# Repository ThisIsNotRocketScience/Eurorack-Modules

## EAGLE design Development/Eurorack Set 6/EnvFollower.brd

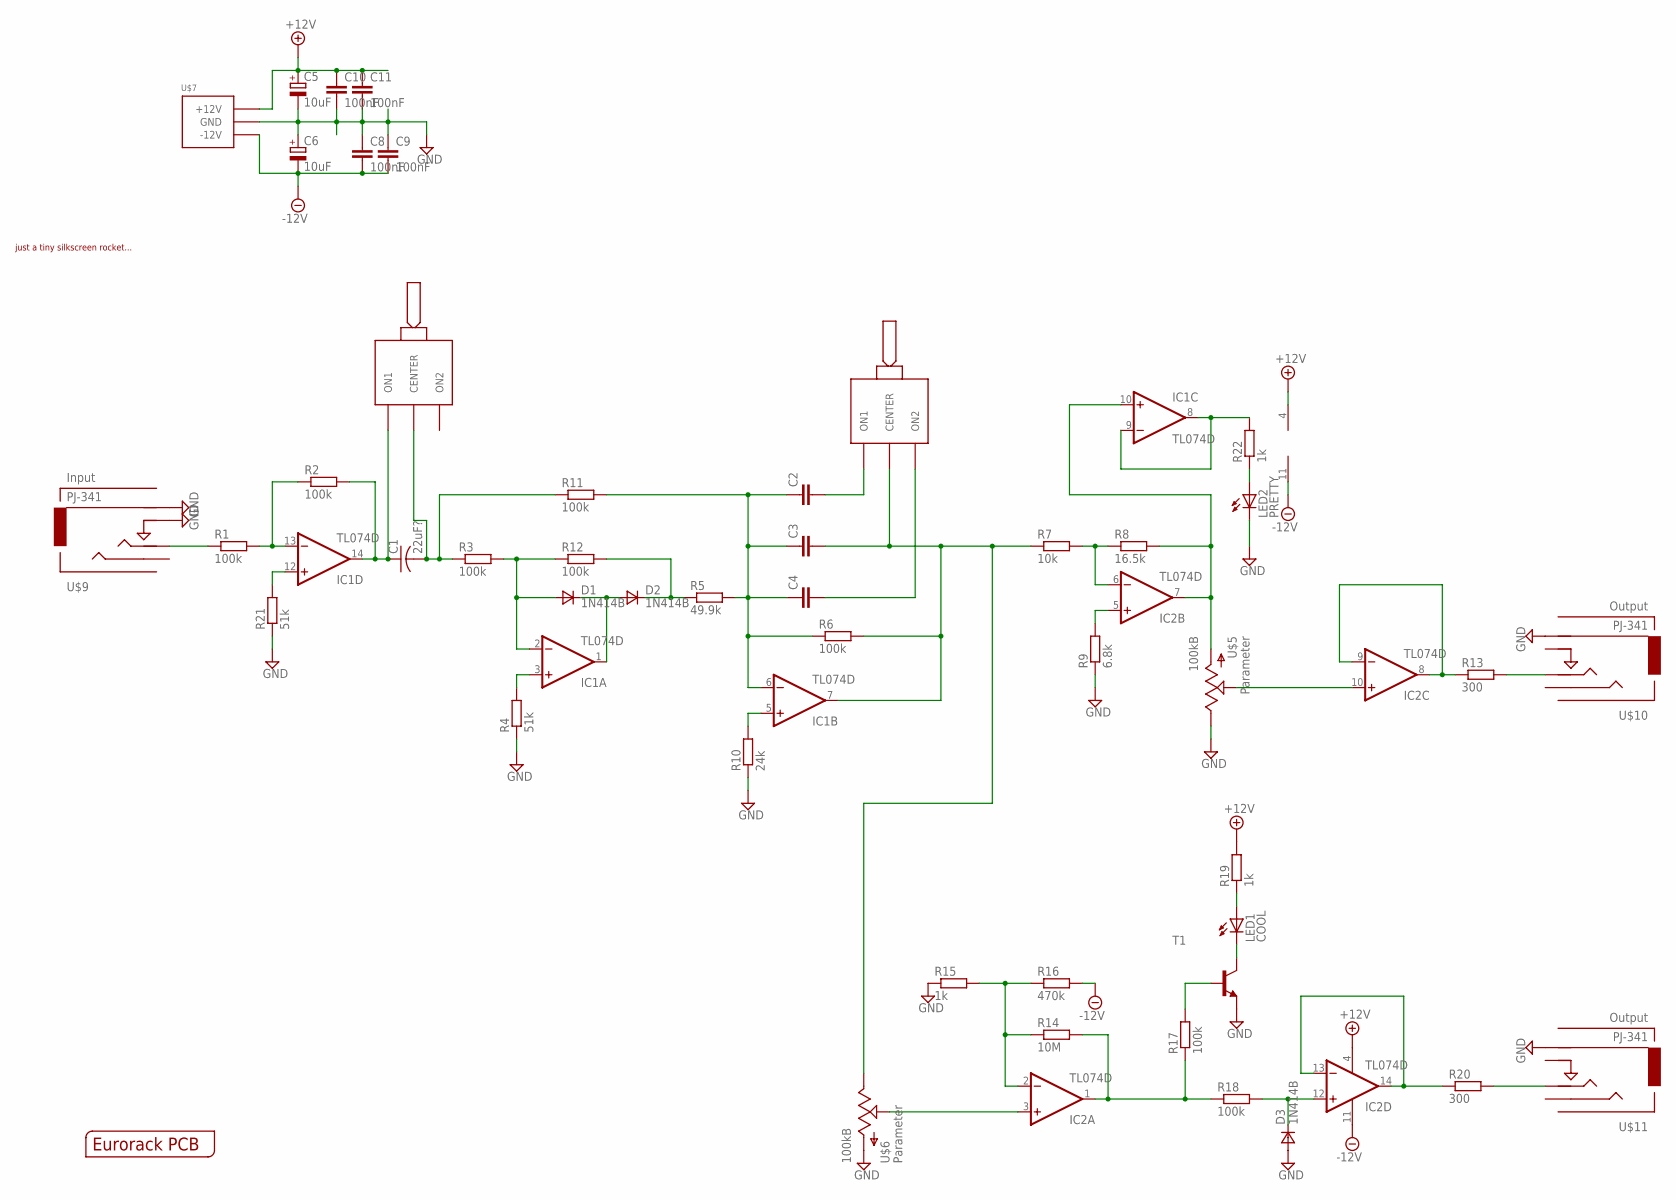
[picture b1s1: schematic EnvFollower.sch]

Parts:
C1: 22uF?; C1210K
C2, C3, C4: C-EUC0603K; C0603K
C5, C6: 10uF; 153CLV-0505
C8, C9, C10, C11: 100nF; C0603K
D1, D2, D3: 1N414B; SOT-23
IC1, IC2: TL074D; SO14
LED1: COOL; LED3MM
LED2: PRETTY; LED3MM
R1, R2, R3, R6, R11, R12, R17, R18: 100k; R0603
R4, R21: 51k; R0603
R5: 49.9k; R0603
R7: 10k; R0603
R8: 16.5k; R0603
R9: 6.8k; R0603
R10: 24k; R0603
R13, R20: 300; R0603
R14: 10M; R0603
R15, R19, R22: 1k; R0603
R16: 470k; R0603
T1: BCX70-NPN-SOT23-BEC; SOT23-BEC
U$1: EURORACK_PCB4HP; EURORACK4HPPCB
U$2: JUSTATINYROCKET
U$4, U$8: ONOFFON; MULTICOMP1MS-ONOFFON
U$5, U$6: 100kB; OG-POTS_ALPS_POT_VERTICAL
U$7: POWER_SIMPLE10-OTHERSIDE; POWER_10_LABELSOTHERSIDE
U$9: PJ-341; 3.5MM-JACK-SWITCH-13MM-INPUT
U$10, U$11: PJ-341; 3.5MM-JACK-SWITCH-13MM-OUTPUT

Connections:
+12V: C5.+, C10.1, C11.1, IC1.4 (V+), IC2.4 (V+), R19.2, U$7.9 (+12V), U$7.10 (+12V)
-12V: C6.-, C8.2, C9.2, IC1.11 (V-), IC2.11 (V-), R16.2, U$7.1 (-12V), U$7.2 (-12V)
GND: C5.-, C6.+, C8.1, C9.1, C10.2, C11.2, D3.3 (A), LED2.K (C), R4.1, R9.1, R10.1, R15.1, R21.1, T1.E, U$5.P$1 (E), U$6.P$3 (A), U$7.3 (GND), U$7.4 (GND), U$7.5 (GND), U$7.6 (GND), U$7.7 (GND), U$7.8 (GND), U$9.RING@3 (RING), U$9.SWITCH@3 (SWITCH), U$10.RING@3 (RING), U$11.RING@3 (RING)
unnamed: IC1.8 (OUT), IC1.9 (-IN), R22.2
unnamed: D2.1 (C), R5.1, R12.2
unnamed: C2.1, C3.1, C4.1, IC1.6 (-IN), R5.2, R6.1, R11.2
unnamed: R1.1, U$9.TIP@3 (TIP)
unnamed: IC1.13 (-IN), R1.2, R2.1
unnamed: C1.2, R3.1, R11.1, U$4.2 (CENTER)
unnamed: C1.1, IC1.14 (OUT), R2.2, U$4.1 (ON1)
unnamed: LED2.A, R22.1
unnamed: D1.3 (A), IC1.2 (-IN), R3.2, R12.1
unnamed: D1.1 (C), D2.3 (A), IC1.1 (OUT)
unnamed: IC1.3 (+IN), R4.2
unnamed: IC1.12 (+IN), R21.2
unnamed: C3.2, IC1.7 (OUT), R6.2, R7.1, U$6.P$1 (E), U$8.2 (CENTER)
unnamed: C2.2, U$8.1 (ON1)
unnamed: C4.2, U$8.3 (ON2)
unnamed: IC1.5 (+IN), R10.2
unnamed: IC2.6 (-IN), R7.2, R8.1
unnamed: IC2.5 (+IN), R9.2
unnamed: IC1.10 (+IN), IC2.7 (OUT), R8.2, U$5.P$3 (A)
unnamed: IC2.10 (+IN), U$5.P$2 (S)
unnamed: IC2.8 (OUT), IC2.9 (-IN), R13.1
unnamed: R13.2, U$10.TIP@3 (TIP)
unnamed: IC2.2 (-IN), R14.1, R15.2, R16.1
unnamed: IC2.1 (OUT), R14.2, R17.1, R18.1
unnamed: R17.2, T1.B
unnamed: LED1.K (C), T1.C
unnamed: LED1.A, R19.1
unnamed: D3.1 (C), IC2.12 (+IN), R18.2
unnamed: IC2.13 (-IN), IC2.14 (OUT), R20.1
unnamed: R20.2, U$11.TIP@3 (TIP)
unnamed: IC2.3 (+IN), U$6.P$2 (S)

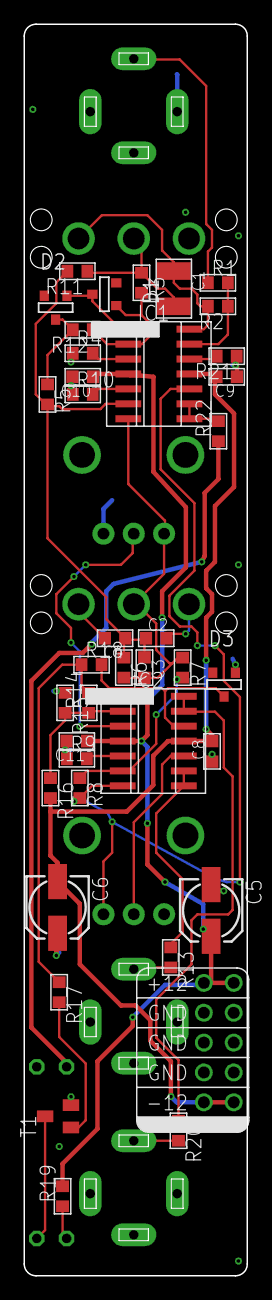
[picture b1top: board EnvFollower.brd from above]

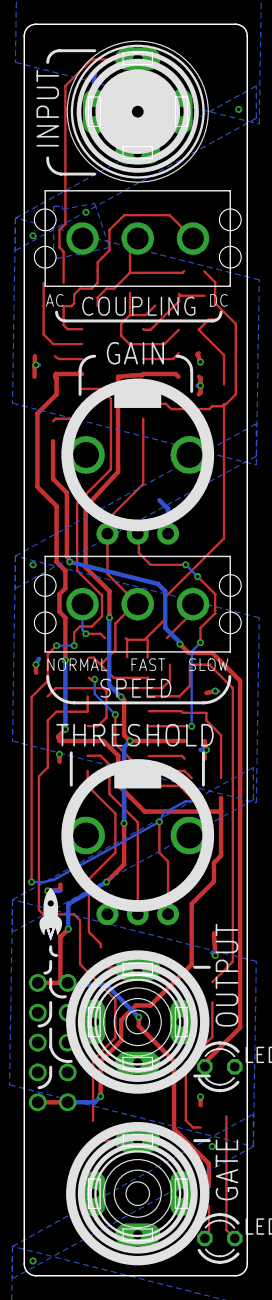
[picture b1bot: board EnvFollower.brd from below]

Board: 2 copper layers, 19.0 x 106.5 mm, 50 parts (11 on the bottom side), 34 nets.

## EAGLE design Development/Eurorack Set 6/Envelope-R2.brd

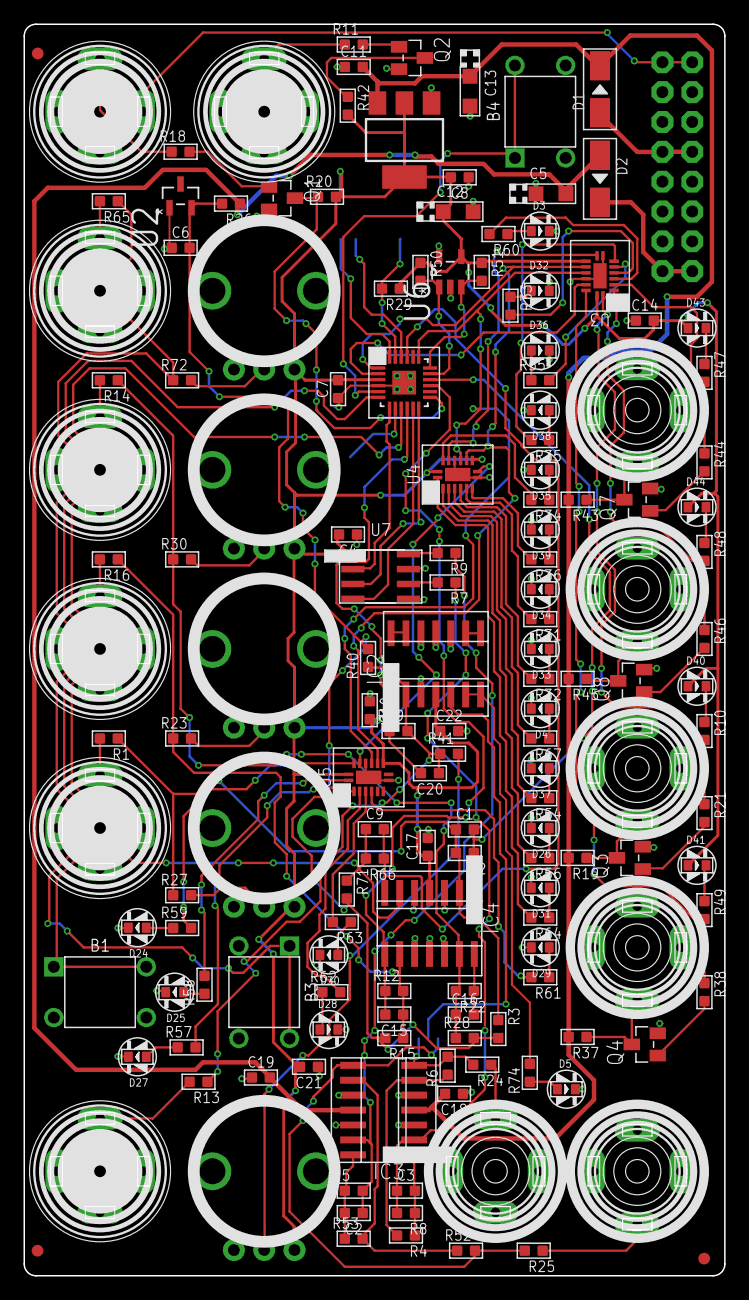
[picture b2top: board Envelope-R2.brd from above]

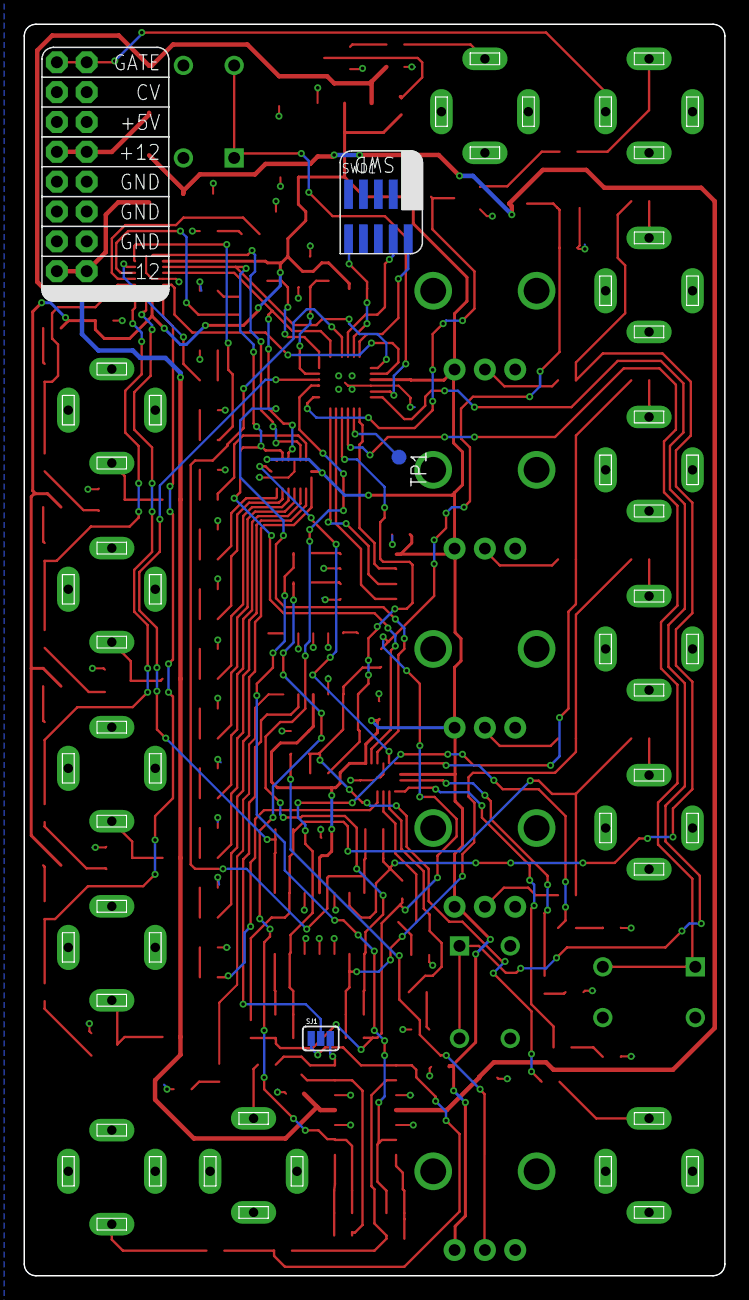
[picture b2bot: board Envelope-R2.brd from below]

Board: 2 copper layers, 59.6 x 106.5 mm, 162 parts (4 on the bottom side), 120 nets.

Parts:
B1, B3, B4: BUTTON-4P-3110040P1; 4P-6.0X6.0X5.0H
C1, C2, C3, C9, C15, C16, C20: 3.3nF; C0603
C4, C6, C7, C8, C10, C11, C14, C17, C18, C19, C21, C22: 100nF; C0603
C5, C12, C13: 10uF; AVX-A
D1, D2: MRA4004T3G; DO-214AC
D3, D4, D5, D24, D25, D26, D27, D28, D29, D30, D31, D32, D33, D34, D35, D36, D37, D38, D39, D40, D41, D43, D44: yellow; LED0603
FID1, FID2, FID3: FIDUCIAL; FIDUCIAL_1MM
IC1: LD1117AS33TR; SOT223
IC2, IC4: MCP6004; SO14
IC3: TL074D; SO14
J1, J2, J3, J4, J5, J6, J15: PJ-341; 3.5MM-JACK-SWITCH-13MM-INPUT
J7, J8, J10, J11, J12, J13: PJ-341; 3.5MM-JACK-SWITCH-13MM-OUTPUT
J14: POWER; POWER_16
OUTLINE: EURORACK_PCB12HP; EURORACK12HPPCB
Q1, Q2, Q3, Q4, Q7, Q8: MMBT3904; SOT23-BEC
R1, R4, R6, R11, R13, R14, R16, R18, R21, R38, R44, R46, R52, R53, R65: 100k; R0603
R2, R12, R22, R23, R27, R30, R39, R41, R66, R72: 33k; R0603
R3, R15, R28, R40, R71: 51k; R0603
R5, R8: 30k; R0603
R7, R9: 12k; R0603
R10, R31, R32, R33, R34, R35, R36, R47, R48, R49, R54, R55, R56, R57, R58, R59, R60, R61, R62, R63, R64, R67, R74: 56; R0603
R17, R68, R69, R70, R73: 10kB; OG-POTS_ALPS_POT_VERTICAL
R19, R20, R26, R29, R37, R42, R43, R45: 10k; R0603
R24, R25: 100; R0603
R50, R51: 2k; R0603
SJ1: SJ_3_PASTE1&2
SWD1: CORTEX_SWD; M50-3600542
TP1: TPB1,27; B1,27
U1: MKL02Z32VFK4; QFN50P400X400X100-25N
U2: LM4040DIM3-5.0; SOT95P237X112-3N
U3, U4, U5: 74HC595BQ; QFN50P250X350X100-17N
U6: 24LC16T-I/OT; SOT95P290X145-5N
U7: MCP4822-E/SN; SOIC8-N_MC

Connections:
3.3V: C4.2, C7.2, C8.2, C10.2, C12.+, C14.2, C17.1, C21.2, C22.1, D40.+, D41.+, D43.+, D44.+, IC1.2, IC1.4, IC2.4, IC4.4, R17.P$3, R20.2, R29.1, R42.2, R50.1, R51.1, R68.P$3, R69.P$3, R70.P$3, R73.P$3, SWD1.1, U1.3, U3.10, U3.16, U4.10, U4.16, U5.10, U5.16, U6.4, U7.1
12V: C11.2, C13.+, C18.2, D1.2, IC1.3, IC3.4, R19.2, R37.2, R43.2, R45.2
-12V: C5.-, C19.2, D2.1, IC3.11, R26.1
ADC_ATTACK: C9.2, IC4.7, R66.1, U1.21
ADC_CURVE: C20.2, IC2.1, R39.1, U1.10
ADC_DECAY: C16.2, IC4.14, R22.1, U1.14
ADC_RELEASE: C1.2, IC4.1, R2.1, U1.16
ADC_SUSTAIN: C15.2, IC4.8, R12.1, U1.15
BUTTON_LOOP: B3.1, B3.4, U1.6
BUTTON_TIMERANGE: B1.1, B1.4, U1.9
BUTTON_TRIGGER: B4.1, B4.4, U1.5
CLOCK: U1.1, U3.11, U4.11, U5.11
CPU_RESET: R29.2, SWD1.10, U1.23
D21: D43.-, R47.1
DACCS: U1.7, U7.2
DACSCK: U1.12, U7.3
DACSDI: U1.11, U7.4
EXTGATE: J5.SWITCH@3, J14.15, J14.16
GND: B1.2, B1.3, B3.2, B3.3, B4.2, B4.3, C4.1, C5.+, C6.1, C7.1, C8.1, C10.1, C11.1, C12.-, C13.-, C14.1, C17.2, C18.1, C19.1, C21.1, C22.2, D3.-, D4.-, D5.-, D24.-, D25.-, D26.-, D27.-, D28.-, D29.-, D30.-, D31.-, D32.-, D33.-, D34.-, D35.-, D36.-, D37.-, D38.-, D39.-, IC1.1, IC2.3, IC2.10, IC2.11, IC2.12, IC3.3, IC3.5, IC3.10, IC3.12, IC4.3, IC4.5, IC4.10, IC4.11, IC4.12, J1.RING@3, J1.SWITCH@3, J2.RING@3, J2.SWITCH@3, J3.RING@3, J3.SWITCH@3, J4.RING@3, J4.SWITCH@3, J5.RING@3, J6.RING@3, J6.SWITCH@3, J7.RING@3, J8.RING@3, J10.RING@3, J11.RING@3, J12.RING@3, J13.RING@3, J14.3, J14.4, J14.5, J14.6, J14.7, J14.8, J15.RING@3, J15.SWITCH@3, Q1.E, Q2.E, Q3.E, Q4.E, Q7.E, Q8.E, R17.P$1, R68.P$1, R69.P$1, R70.P$1, R73.P$1, SWD1.3, SWD1.5, U1.4, U1.25, U2.1, U3.8, U3.13, U3.17, U4.8, U4.13, U4.17, U5.8, U5.13, U5.17, U6.2, U6.5, U7.5, U7.7
KNOB_ATTACK: R72.2, R73.P$2
KNOB_CURVE: R41.2, R70.P$2
KNOB_DECAY: R17.P$2, R30.2
KNOB_RELEASE: R27.2, R69.P$2
KNOB_SUSTAIN: R23.2, R68.P$2
LATCH: U1.19, U3.12, U4.12, U5.12
unnamed: IC2.8, IC2.9
unnamed: IC3.6, R4.2, R6.1
unnamed: J2.TIP@3, R16.2
unnamed: C15.1, IC4.9, R12.2, R15.1, R16.1, R23.1
unnamed: R9.2, U7.8
unnamed: J3.TIP@3, R1.2
unnamed: R7.2, U7.6
unnamed: C1.1, IC4.2, R1.1, R2.2, R3.1, R27.1
unnamed: C2.1, IC3.13, R5.2, R9.1
unnamed: C3.1, IC3.2, R7.1, R8.2
unnamed: J15.TIP@3, R65.2
unnamed: J4.TIP@3, R13.2
unnamed: D1.1, J14.9, J14.10
unnamed: R36.2, U4.7
unnamed: Q1.B, R18.2
unnamed: J5.TIP@3, R18.1
unnamed: IC3.9, R52.1, R53.2
unnamed: C3.2, IC3.1, R4.1, R8.1
unnamed: IC2.6, IC2.7, R74.2
unnamed: J13.TIP@3, R25.1
unnamed: J12.TIP@3, R24.1
unnamed: C9.1, IC4.6, R65.1, R66.2, R71.1, R72.1
unnamed: D40.-, R10.1
unnamed: C2.2, IC3.14, R5.1, R53.1
unnamed: Q3.B, R21.2
unnamed: IC2.13, IC2.14
unnamed: R31.2, U4.6
unnamed: D28.+, R62.1
unnamed: J7.TIP@3, Q3.C, R19.1
unnamed: D4.+, R67.1
unnamed: R60.2, U3.4
unnamed: D29.+, R61.1
unnamed: J1.TIP@3, R14.2
unnamed: C16.1, IC4.13, R14.1, R22.2, R28.1, R30.1
unnamed: R33.2, U3.5
unnamed: R55.2, U3.6
unnamed: R35.2, U3.7
unnamed: R34.2, U4.15
unnamed: R32.2, U4.5
unnamed: R67.2, U4.4
unnamed: R54.2, U4.3
unnamed: R56.2, U4.2
unnamed: Q2.B, R11.2
unnamed: D41.-, R49.1
unnamed: D44.-, R48.1
unnamed: C20.1, IC2.2, R13.1, R39.2, R40.1, R41.1
unnamed: J6.TIP@3, R11.1
unnamed: R64.2, U4.1
unnamed: R61.2, U5.5
unnamed: R59.2, U5.15
unnamed: D3.+, R60.1
unnamed: R58.2, U5.1
unnamed: R57.2, U5.2
unnamed: R62.2, U5.3
unnamed: R63.2, U5.4
unnamed: Q4.B, R38.2
unnamed: J8.TIP@3, Q4.C, R37.1
unnamed: D5.+, R74.1
unnamed: IC2.5, SJ1.2
unnamed: D2.2, J14.1, J14.2
unnamed: Q7.B, R44.2
unnamed: J10.TIP@3, Q7.C, R43.1
unnamed: Q8.B, R46.2
unnamed: J11.TIP@3, Q8.C, R45.1
unnamed: D27.+, R57.1
unnamed: D26.+, R56.1
unnamed: D25.+, R58.1
unnamed: D24.+, R59.1
unnamed: D30.+, R63.1
unnamed: D31.+, R64.1
unnamed: D32.+, R33.1
unnamed: D33.+, R32.1
unnamed: D34.+, R31.1
unnamed: D35.+, R34.1
unnamed: D36.+, R55.1
unnamed: D37.+, R54.1
unnamed: D38.+, R35.1
unnamed: D39.+, R36.1
OUT_ATTACK: R44.1, R47.2, U3.3
OUT_CUR_PRERES: IC3.8, R25.2, R52.2, SJ1.1
OUT_DECAY: R46.1, R48.2, U3.2
OUT_LIN_PRERES: IC3.7, R6.2, R24.2, SJ1.3
OUT_RELEASEDONE: R38.1, R49.2, U3.15
OUT_RELEASESTART: R10.2, R21.1, U3.1
PTA6: TP1.TP, U1.8
REF_-5V: C6.2, R3.2, R15.2, R26.2, R28.2, R40.2, R71.2, U2.2
RETRIGGER_ENVELOPE: Q2.C, R42.1, U1.20
SCL: R50.2, U1.17, U6.1
SDA: R51.2, U1.18, U6.3
SHIFTER1TO2: U3.9, U4.14
SHIFTER2TO3: U4.9, U5.14
SHIFTERS: U1.2, U3.14
SWD_CLK: SWD1.4, U1.22
SWD_DIO: SWD1.2, U1.24
TRIGGER_ENVELOPE: Q1.C, R20.1, U1.13

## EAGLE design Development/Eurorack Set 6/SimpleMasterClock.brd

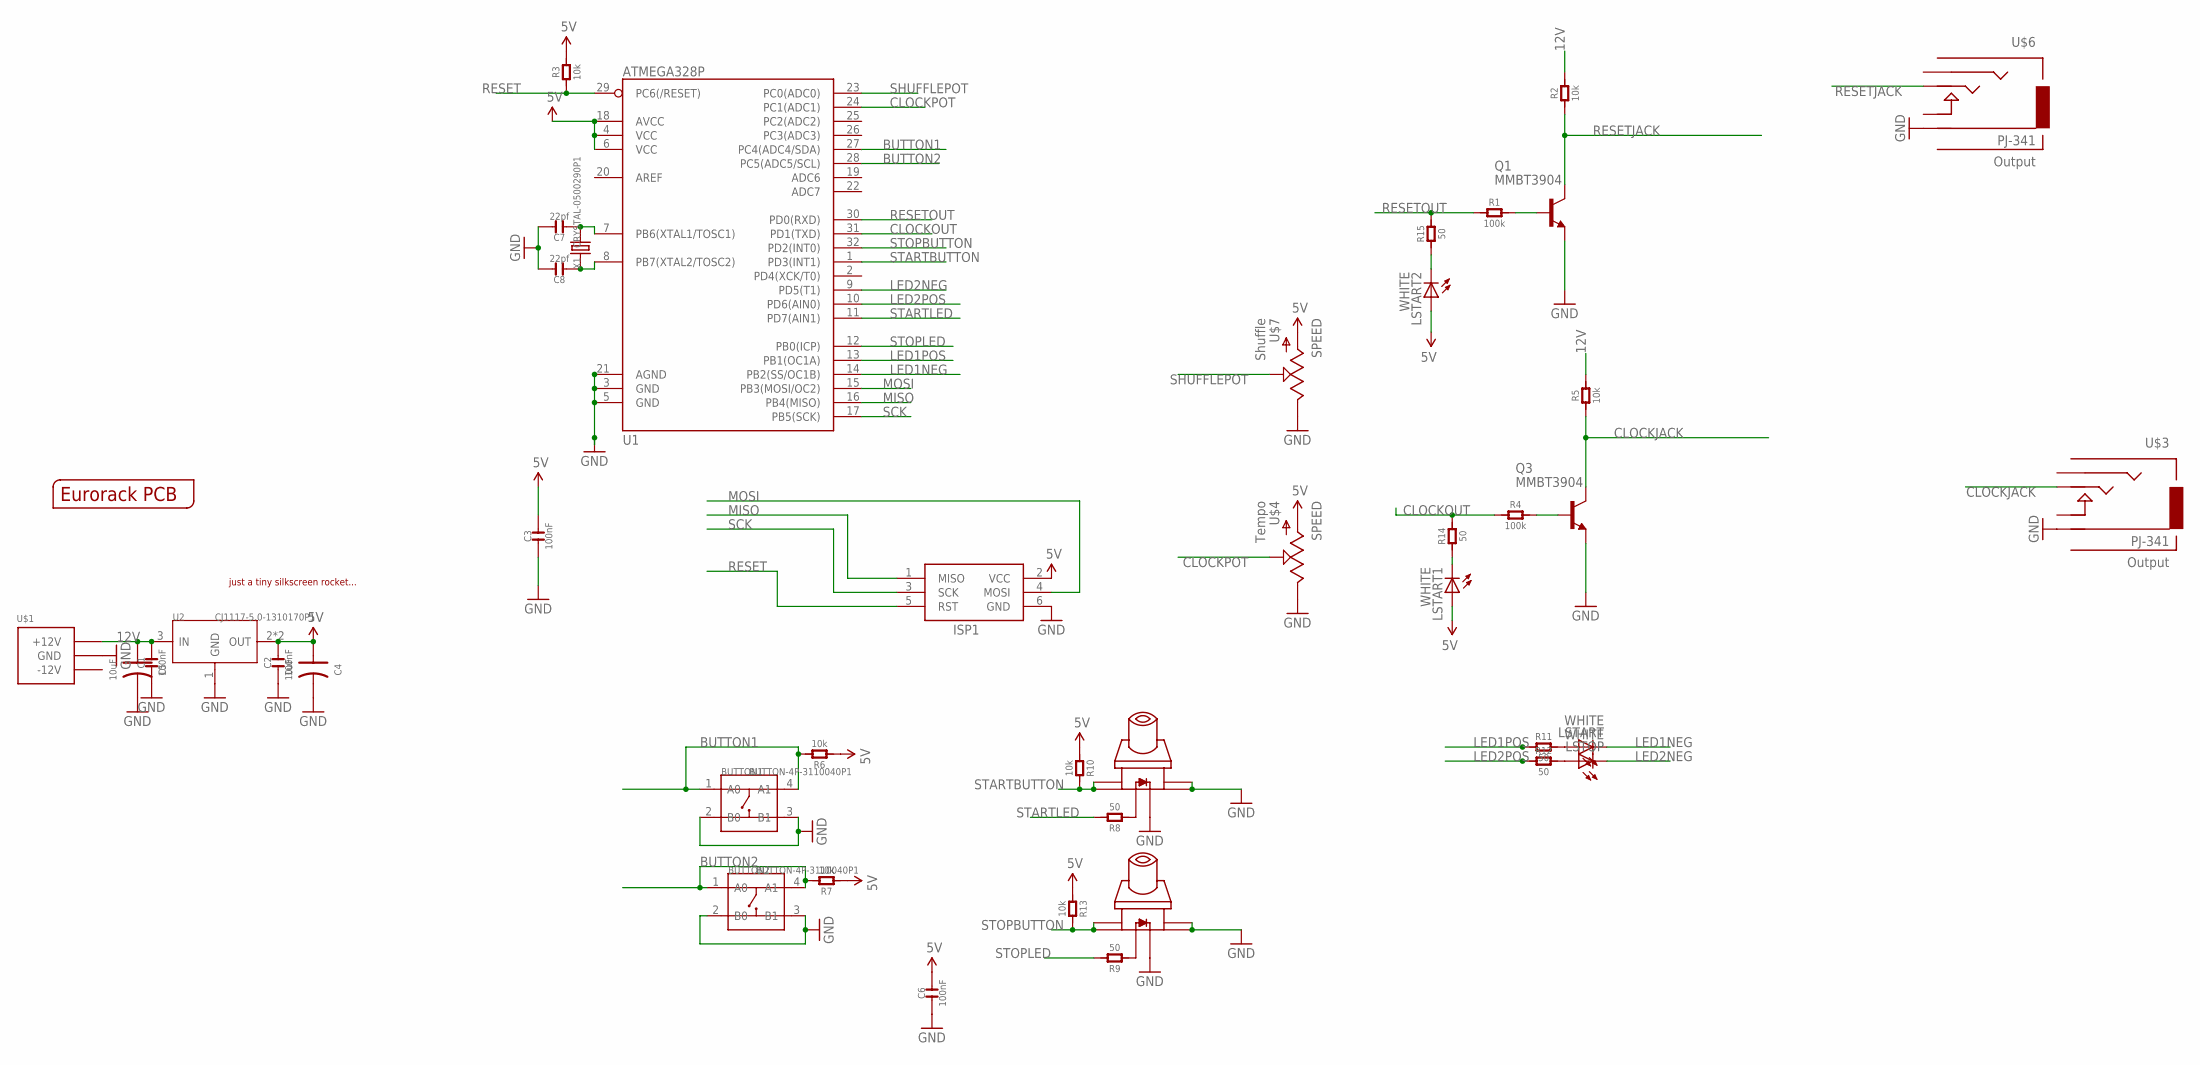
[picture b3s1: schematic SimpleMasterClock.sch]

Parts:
BUTTON1, BUTTON2: BUTTON-4P-3110040P1; 4P-6.0X6.0X5.0H
C1, C2, C3, C6: 100nF; C0603
C4, C5: 10uF; AVX-A
C7, C8: 22pf; C0603
ISP1: AVRISP-6; AVRISP
LSTART, LSTART1, LSTART2: WHITE; LED3MM
LSTOP: WHITE; LED3MM
Q1, Q3: MMBT3904; SOT23-BEC
R1, R4: 100k; R0603
R2, R3, R5, R6, R7, R10, R13: 10k; R0603
R8, R9, R11, R12, R14, R15: 50; R0603
START: SWITCH_W_LED_PB6149L-X-102WHITE; PB6149L
STOP: SWITCH_W_LED_PB6149L-X-102WHITE; PB6149L
U1: ATMEGA328P; TQFP32-08
U2: CJ1117-5.0-1310170P1; SOT223
U$1: POWER_SIMPLE10-OTHERSIDE; POWER_10_LABELSOTHERSIDE
U$2: EURORACK_PCB4HP; EURORACK4HPPCB
U$3, U$6: PJ-341; 3.5MM-JACK-SWITCH-13MM-OUTPUT
U$4, U$7: SPEED; OG-POTS_ALPS_POT_VERTICAL
U$5: JUSTATINYROCKET
X1: CRYSTAL-0500290P1; 2P-SMD-5.0X3.2

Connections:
5V: C2.2, C3.2, C4.+ (1), C6.2, ISP1.2 (VCC), LSTART1.A, LSTART2.A, R3.2, R6.1, R7.1, R10.1, R13.1, U1.4 (VCC), U1.6 (VCC), U1.18 (AVCC), U2.2 (OUT), U2.TER (OUT), U$4.P$3 (A), U$7.P$3 (A)
12V: C1.2, C5.+ (1), R2.2, R5.2, U2.3 (IN), U$1.9 (+12V), U$1.10 (+12V)
BUTTON1: BUTTON1.1 (A0), BUTTON1.4 (A1), R6.2, U1.27 (PC4(ADC4/SDA))
BUTTON2: BUTTON2.1 (A0), BUTTON2.4 (A1), R7.2, U1.28 (PC5(ADC5/SCL))
CLOCKJACK: Q3.C, R5.1, U$3.TIP@3 (TIP)
CLOCKOUT: R4.1, R14.2, U1.31 (PD1(TXD))
CLOCKPOT: U1.24 (PC1(ADC1)), U$4.P$2 (S)
GND: BUTTON1.2 (B0), BUTTON1.3 (B1), BUTTON2.2 (B0), BUTTON2.3 (B1), C1.1, C2.1, C3.1, C4.- (2), C5.- (2), C6.1, C7.2, C8.2, ISP1.6 (GND), Q1.E, Q3.E, START.3, START.4, START.LEDNEG (NEG), STOP.3, STOP.4, STOP.LEDNEG (NEG), U1.3 (GND), U1.5 (GND), U1.21 (AGND), U2.1 (GND), U$1.3 (GND), U$1.4 (GND), U$1.5 (GND), U$1.6 (GND), U$1.7 (GND), U$1.8 (GND), U$3.RING@3 (RING), U$4.P$1 (E), U$6.RING@3 (RING), U$7.P$1 (E)
LED1NEG: LSTART.K (C), U1.14 (PB2(SS/OC1B))
LED1POS: R11.1, U1.13 (PB1(OC1A))
LED2NEG: LSTOP.K (C), U1.9 (PD5(T1))
LED2POS: R12.1, U1.10 (PD6(AIN0))
MISO: ISP1.1 (MISO), U1.16 (PB4(MISO))
MOSI: ISP1.4 (MOSI), U1.15 (PB3(MOSI/OC2))
unnamed: LSTART.A, R11.2
unnamed: LSTOP.A, R12.2
unnamed: R8.1, START.LEDPOS (POS)
unnamed: R9.1, STOP.LEDPOS (POS)
unnamed: C7.1, U1.7 (PB6(XTAL1/TOSC1)), X1.2
unnamed: C8.1, U1.8 (PB7(XTAL2/TOSC2)), X1.1
unnamed: LSTART1.K (C), R14.1
unnamed: LSTART2.K (C), R15.1
unnamed: Q3.B, R4.2
unnamed: Q1.B, R1.2
RESET: ISP1.5 (RST), R3.1, U1.29 (PC6(/RESET))
RESETJACK: Q1.C, R2.1, U$6.TIP@3 (TIP)
RESETOUT: R1.1, R15.2, U1.30 (PD0(RXD))
SCK: ISP1.3 (SCK), U1.17 (PB5(SCK))
SHUFFLEPOT: U1.23 (PC0(ADC0)), U$7.P$2 (S)
STARTBUTTON: R10.2, START.1, START.2, U1.1 (PD3(INT1))
STARTLED: R8.2, U1.11 (PD7(AIN1))
STOPBUTTON: R13.2, STOP.1, STOP.2, U1.32 (PD2(INT0))
STOPLED: R9.2, U1.12 (PB0(ICP))

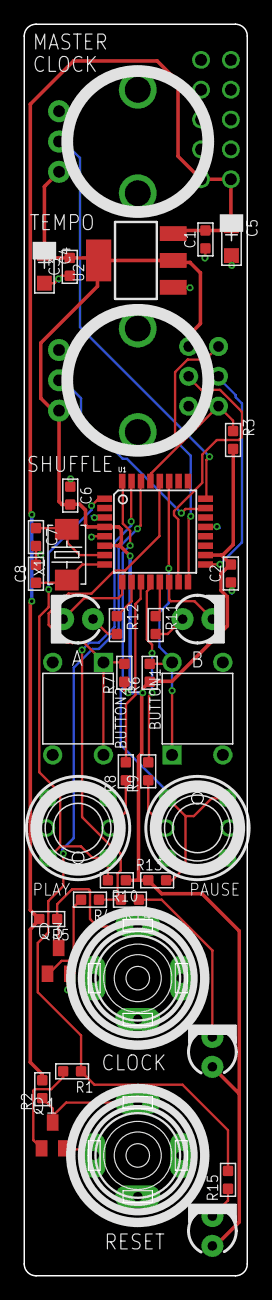
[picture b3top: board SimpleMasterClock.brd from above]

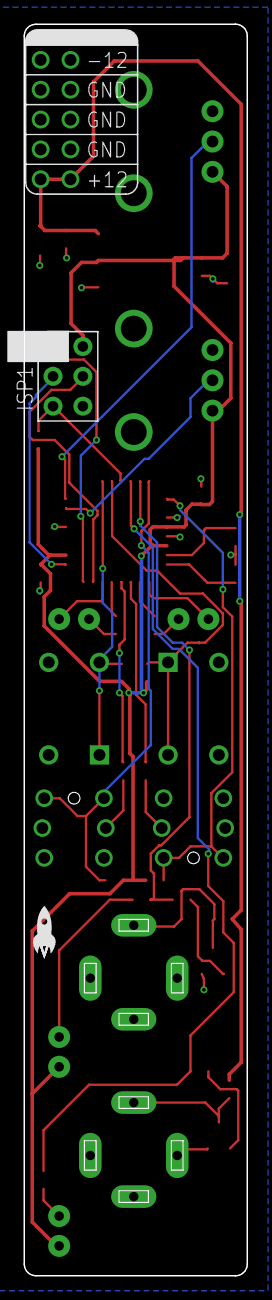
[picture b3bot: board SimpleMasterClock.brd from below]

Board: 2 copper layers, 19.0 x 106.5 mm, 44 parts (3 on the bottom side), 33 nets.

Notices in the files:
parts and their libraries:
SparkFun-Passives: Licensing: CC v3.0 Share-Alike You are welcome to use this library for commercial purposes.
